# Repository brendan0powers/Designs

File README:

I should probably put some info here.

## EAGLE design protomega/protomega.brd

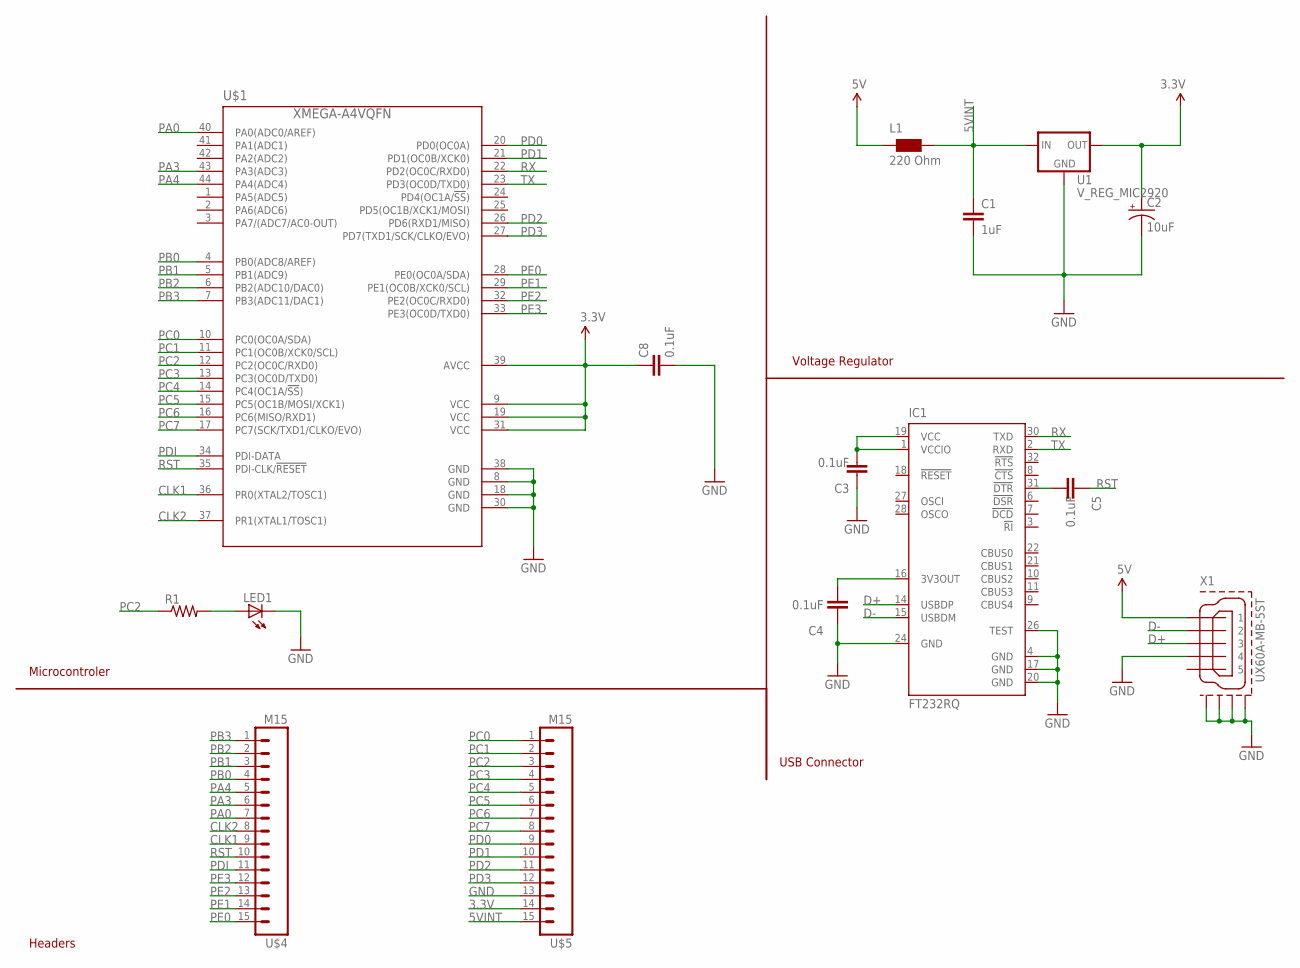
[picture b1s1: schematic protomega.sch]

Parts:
C1: 1uF; C0603
C2: 10uF; EIA3216
C3, C4, C5, C8: 0.1uF; C0603
IC1: FT232RQ; QFN32
L1: 220 Ohm; 0603
LED1: LEDSMT1206; 1206
R1: R-US_R0603; R0603
U1: V_REG_MIC2920; SOT223
U$1: XMEGA-A4VQFN; QFN44
U$4, U$5: M15; 1X15
X1: UX60A-MB-5ST

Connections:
3.3V: C2.A (+), C8.1, U1.3 (OUT), U$1.9 (VCC), U$1.19 (VCC), U$1.31 (VCC), U$1.39 (AVCC), U$5.14
5V: L1.1, X1.1
5VINT: C1.1, L1.2, U1.1 (IN), U$5.15
CLK1: U$1.36 (PR0(XTAL2/TOSC1)), U$4.9
CLK2: U$1.37 (PR1(XTAL1/TOSC1)), U$4.8
D+: IC1.14 (USBDP), X1.3
D-: IC1.15 (USBDM), X1.2
GND: C1.2, C2.C (-), C3.1, C4.1, C8.2, IC1.4 (GND), IC1.17 (GND), IC1.20 (GND), IC1.24 (GND), IC1.26 (TEST), LED1.C, U1.2 (GND), U$1.8 (GND), U$1.18 (GND), U$1.30 (GND), U$1.38 (GND), U$5.13, X1.4, X1.M1 (GND1), X1.M2 (GND2), X1.M3 (GND3), X1.M4 (GND4)
unnamed: C3.2, IC1.1 (VCCIO), IC1.19 (VCC)
unnamed: LED1.A, R1.2
unnamed: C4.2, IC1.16 (3V3OUT)
unnamed: C5.2, IC1.31 (!DTR)
PA0: U$1.40 (PA0(ADC0/AREF)), U$4.7
PA3: U$1.43 (PA3(ADC3)), U$4.6
PA4: U$1.44 (PA4(ADC4)), U$4.5
PB0: U$1.4 (PB0(ADC8/AREF)), U$4.4
PB1: U$1.5 (PB1(ADC9)), U$4.3
PB2: U$1.6 (PB2(ADC10/DAC0)), U$4.2
PB3: U$1.7 (PB3(ADC11/DAC1)), U$4.1
PC0: U$1.10 (PC0(OC0A/SDA)), U$5.1
PC1: U$1.11 (PC1(OC0B/XCK0/SCL)), U$5.2
PC2: R1.1, U$1.12 (PC2(OC0C/RXD0)), U$5.3
PC3: U$1.13 (PC3(OC0D/TXD0)), U$5.4
PC4: U$1.14 (PC4(OC1A/!SS!)), U$5.5
PC5: U$1.15 (PC5(OC1B/MOSI/XCK1)), U$5.6
PC6: U$1.16 (PC6(MISO/RXD1)), U$5.7
PC7: U$1.17 (PC7(SCK/TXD1/CLKO/EVO)), U$5.8
PD0: U$1.20 (PD0(OC0A)), U$5.9
PD1: U$1.21 (PD1(OC0B/XCK0)), U$5.10
PD2: U$1.26 (PD6(RXD1/MISO)), U$5.11
PD3: U$1.27 (PD7(TXD1/SCK/CLKO/EVO)), U$5.12
PDI: U$1.34 (PDI-DATA), U$4.11
PE0: U$1.28 (PE0(OC0A/SDA)), U$4.15
PE1: U$1.29 (PE1(OC0B/XCK0/SCL)), U$4.14
PE2: U$1.32 (PE2(OC0C/RXD0)), U$4.13
PE3: U$1.33 (PE3(OC0D/TXD0)), U$4.12
RST: C5.1, U$1.35 (PDI-CLK/!RESET), U$4.10
RX: IC1.30 (TXD), U$1.22 (PD2(OC0C/RXD0))
TX: IC1.2 (RXD), U$1.23 (PD3(OC0D/TXD0))

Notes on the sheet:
Headers
Voltage Regulator
Microcontroler
USB Connector

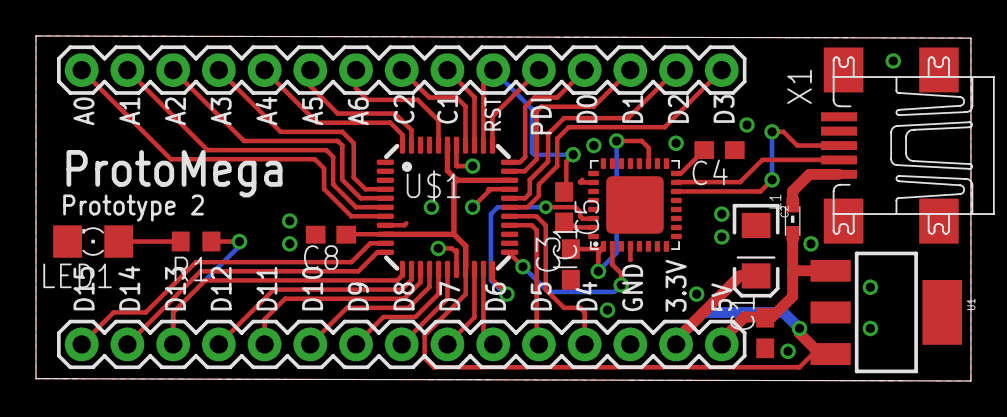
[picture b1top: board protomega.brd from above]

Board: 2 copper layers, 51.9 x 19.2 mm, 16 parts (1 on the bottom side), 39 nets.

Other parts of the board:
U$6: OSHW-LOGO-S

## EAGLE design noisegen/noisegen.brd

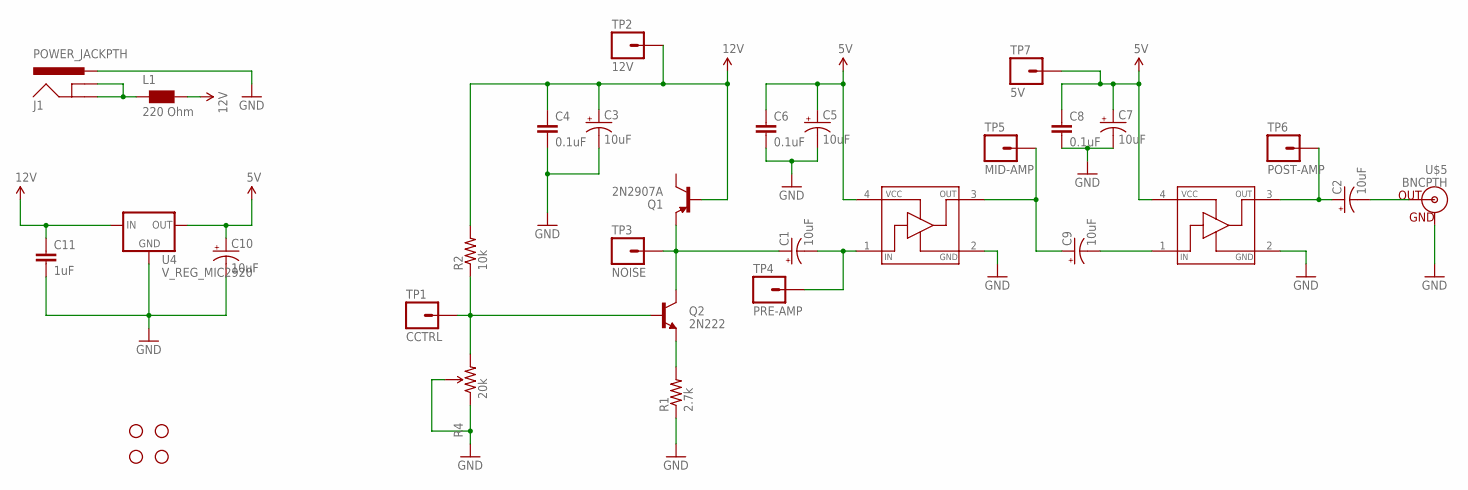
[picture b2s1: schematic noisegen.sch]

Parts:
C1, C2, C3, C5, C7, C9, C10: 10uF; EIA3216
C4, C6, C8: 0.1uF; 0603-CAP
C11: 1uF; C0603
J1: POWER_JACKPTH; POWER_JACK_PTH
JP1, JP2, JP3, JP4: STAND-OFF
L1: 220 Ohm; 0603
Q1: 2N2907A; SOT23-3
Q2: 2N222; SOT23-3
R1: 2.7k; 0603-RES
R2: 10k; 0603-RES
R4: 20k; 3362U-2
TP1: CCTRL; 1X01
TP2: 12V; 1X01
TP3: NOISE; 1X01
TP4: PRE-AMP; 1X01
TP5: MID-AMP; 1X01
TP6: POST-AMP; 1X01
TP7: 5V; 1X01
U4: V_REG_MIC2920; SOT223
U$1, U$2: MAX2650; SOT143
U$5: BNCPTH; BNC

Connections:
5V: C5.A (+), C6.1, C7.A (+), C8.1, C10.A (+), TP7.1, U4.3 (OUT), U$1.4 (VCC), U$2.4 (VCC)
GND: C3.C (-), C4.2, C5.C (-), C6.2, C7.C (-), C8.2, C10.C (-), C11.2, J1.PWR, R1.1, R4.1 (CCW), R4.2 (WIPER), U4.2 (GND), U$1.2 (GND), U$2.2 (GND), U$5.GND
unnamed: C9.C (-), U$2.1 (IN)
unnamed: C1.C (-), TP4.1, U$1.1 (IN)
unnamed: C2.A (+), TP6.1, U$2.3 (OUT)
unnamed: C1.A (+), Q1.2 (E), Q2.3 (C), TP3.1
unnamed: Q2.2 (E), R1.2
unnamed: C2.C (-), U$5.S (OUT)
unnamed: Q2.1 (B), R2.1, R4.3 (CW), TP1.1
unnamed: C9.A (+), TP5.1, U$1.3 (OUT)
unnamed: J1.GND, J1.GNDBREAK, L1.1
VCC: C3.A (+), C4.1, C11.1, L1.2, Q1.1 (B), R2.2, TP2.1, U4.1 (IN)

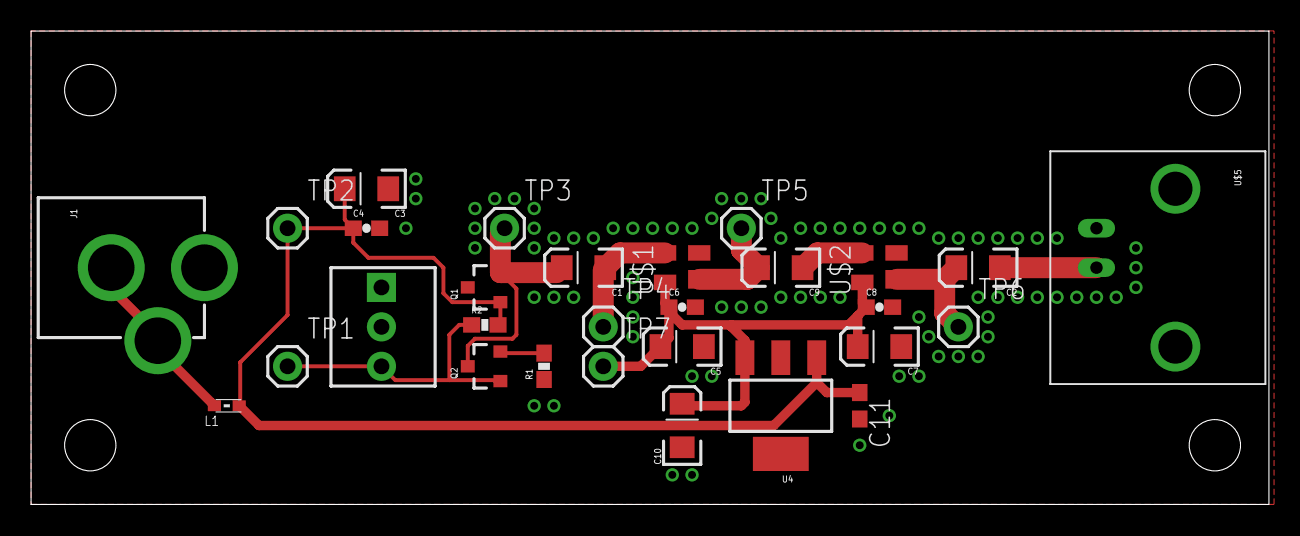
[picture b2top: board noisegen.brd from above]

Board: 2 copper layers, 79.7 x 30.5 mm, 33 parts (0 on the bottom side), 12 nets.

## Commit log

2011-11-13 Initial Import
2011-11-13 Added the first revision of the prototype board
2011-11-17 Moved to 6 mill traces for digital signals Moved to 13mil vias for trace connections, and 15mil vias for ground planes Use only 0605 components and above Extended pads on the XMega package Replace th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
2011-11-18 Did some stuff!
2011-11-22 Cleaned up Xmega board Added new board using the MRF24J40MA Another board using the MRF24J40MA, with 0.1 spaced headers
2011-11-22 Fixed some errors on the new boards
2011-11-23 Added new board that uses a TQFP chip for the xmega Fixed up names Added silk screen to the bottom of the board
2011-11-28 Cleaned up nanonode-xmega-mc-headers-qfp added jumpers for bootloader and OS
2011-11-28 Added a new board that uses the atxmega32a4u
2011-11-28 nanonode-xmega-mc-headers-qfp-a4: Claened up silkscreen and vias
2011-12-10 Added Logo
2011-12-28 Updaed artwork for the nanonode
2011-12-28 Updated nanonode board
2011-12-28 Added gitignore file
2011-12-28 Renamed NanoNode project to ProtoNode
2011-12-29 Added protomega Xmega breakout board
2011-12-30 protonode: Now thinner, added 1 pin to each header, fixed VREG
2011-12-30 protonode: Cleaned up schematic files
2011-12-30 protomega: cleaned up the board a bit
2011-12-30 protomega: slightly reduced the boards heigh
2011-12-30 protomega: Removed pull up resistor on reset line, fixed reset label.
2012-01-15 Added the first revision of the SD card logger
2012-01-16 Added new revision of the sdlogger. New 5cm X 5cm board, SMT, temp sensor, DC jack
2012-01-20 sdlogger: Added power fets and protection resistors
2012-01-20 sdlogger: added resistor valuex
2012-01-21 sdlogger: Replaced some components with through hole versions
2012-01-21 russell was here
2012-01-21 without a trace
2012-01-26 ProtoMega: Removed 2 ADC pins ProtoMega: Broke out Clock Pins ProtoMega: Added LED ProtoMega: Added reset button
2012-01-26 ProtoMega: Updated prototype label
2012-02-01 New version of the protomega board. Moved reset button, LED is on pin13
2012-03-08 Added tinypacket board
2012-03-08 TinyPacket: Cleaned up schematic
2012-03-08 tinypacket: Fixed seperation of the ground planes, and added a via
2012-03-09 tinypacket: Moved audio interface to an opto-isolated design tinypacket: AGND now comes from DAC0, Op amp and voltage devider have been removed tinypacket: Smaller board
2012-03-09 tinypacket: Added some IO headers
2012-03-09 tinypacket: Cleaned up the board a bit more tinypacket: Added 2 more ADC pins
2012-03-09 tinypacket: Fixed header spacing and board size
2012-03-09 tinypacket: Added open hardware logo
2012-10-15 NoiseGen: Initial Commit
2013-01-06 New revision of the ProtoMega board. Now with FTDI chip.

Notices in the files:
parts and their libraries:
sparkfun: Licensing: CC v3.0 Share-Alike You are welcome to use this library for commercial purposes.
